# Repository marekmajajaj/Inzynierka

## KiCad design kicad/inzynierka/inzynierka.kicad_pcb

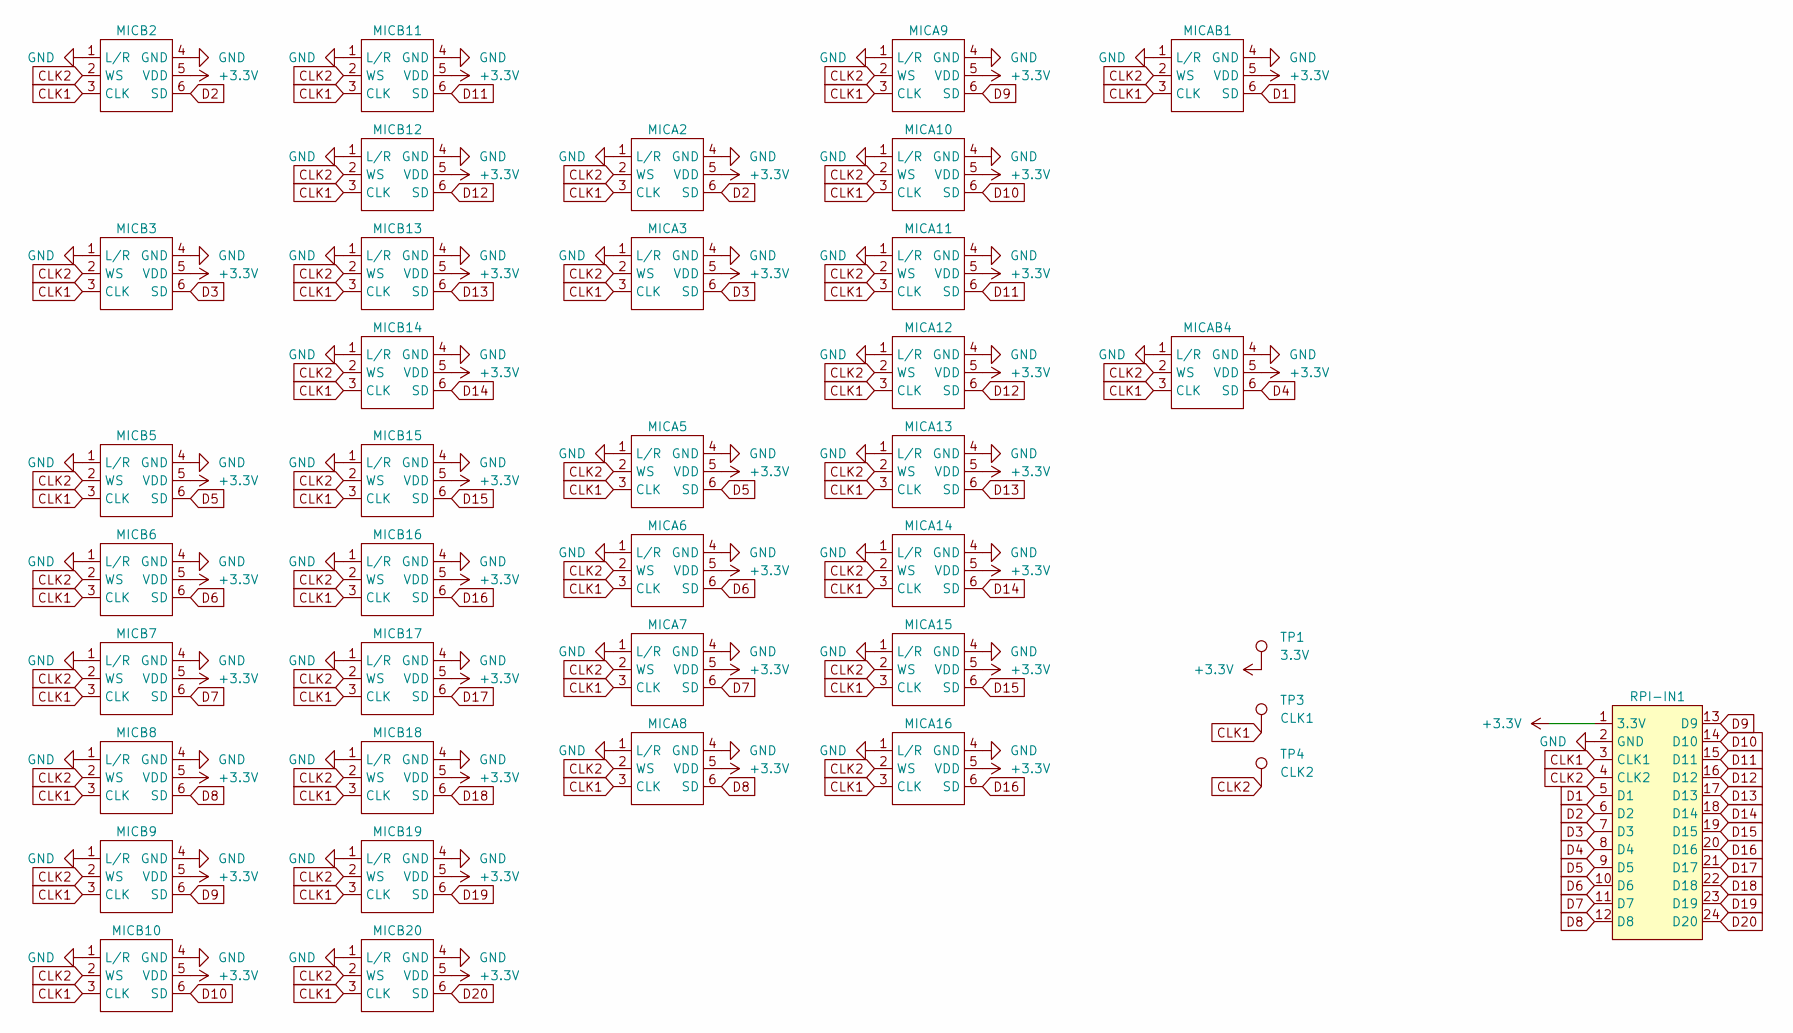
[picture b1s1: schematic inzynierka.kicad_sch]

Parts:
MICA2, MICA3, MICA5, MICA6, MICA7, MICA8, MICA9, MICA10, MICA11, MICA12, MICA13, MICA14, MICA15, MICA16: INMP441 breakout
MICAB1, MICAB4: INMP441 breakout
MICB2, MICB3, MICB5, MICB6, MICB7, MICB8, MICB9, MICB10, MICB11, MICB12, MICB13, MICB14, MICB15, MICB16, MICB17, MICB18, MICB19, MICB20: INMP441 breakout
RPI-IN1: RPI-IN1
TP1: 3.3V
TP3: CLK1
TP4: CLK2

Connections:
+3.3V: MICA2.5 (VDD), MICA3.5 (VDD), MICA5.5 (VDD), MICA6.5 (VDD), MICA7.5 (VDD), MICA8.5 (VDD), MICA9.5 (VDD), MICA10.5 (VDD), MICA11.5 (VDD), MICA12.5 (VDD), MICA13.5 (VDD), MICA14.5 (VDD), MICA15.5 (VDD), MICA16.5 (VDD), MICAB1.5 (VDD), MICAB4.5 (VDD), MICB2.5 (VDD), MICB3.5 (VDD), MICB5.5 (VDD), MICB6.5 (VDD), MICB7.5 (VDD), MICB8.5 (VDD), MICB9.5 (VDD), MICB10.5 (VDD), MICB11.5 (VDD), MICB12.5 (VDD), MICB13.5 (VDD), MICB14.5 (VDD), MICB15.5 (VDD), MICB16.5 (VDD), MICB17.5 (VDD), MICB18.5 (VDD), MICB19.5 (VDD), MICB20.5 (VDD), RPI-IN1.1 (3.3V), TP1.1; also elsewhere on the board
CLK1: MICA2.3 (CLK), MICA3.3 (CLK), MICA5.3 (CLK), MICA6.3 (CLK), MICA7.3 (CLK), MICA8.3 (CLK), MICA9.3 (CLK), MICA10.3 (CLK), MICA11.3 (CLK), MICA12.3 (CLK), MICA13.3 (CLK), MICA14.3 (CLK), MICA15.3 (CLK), MICA16.3 (CLK), MICAB1.3 (CLK), MICAB4.3 (CLK), MICB2.3 (CLK), MICB3.3 (CLK), MICB5.3 (CLK), MICB6.3 (CLK), MICB7.3 (CLK), MICB8.3 (CLK), MICB9.3 (CLK), MICB10.3 (CLK), MICB11.3 (CLK), MICB12.3 (CLK), MICB13.3 (CLK), MICB14.3 (CLK), MICB15.3 (CLK), MICB16.3 (CLK), MICB17.3 (CLK), MICB18.3 (CLK), MICB19.3 (CLK), MICB20.3 (CLK), RPI-IN1.3 (CLK1), TP3.1; also elsewhere on the board
CLK2: MICA2.2 (WS), MICA3.2 (WS), MICA5.2 (WS), MICA6.2 (WS), MICA7.2 (WS), MICA8.2 (WS), MICA9.2 (WS), MICA10.2 (WS), MICA11.2 (WS), MICA12.2 (WS), MICA13.2 (WS), MICA14.2 (WS), MICA15.2 (WS), MICA16.2 (WS), MICAB1.2 (WS), MICAB4.2 (WS), MICB2.2 (WS), MICB3.2 (WS), MICB5.2 (WS), MICB6.2 (WS), MICB7.2 (WS), MICB8.2 (WS), MICB9.2 (WS), MICB10.2 (WS), MICB11.2 (WS), MICB12.2 (WS), MICB13.2 (WS), MICB14.2 (WS), MICB15.2 (WS), MICB16.2 (WS), MICB17.2 (WS), MICB18.2 (WS), MICB19.2 (WS), MICB20.2 (WS), RPI-IN1.4 (CLK2), TP4.1; also elsewhere on the board
D1: MICAB1.6 (SD), RPI-IN1.5 (D1)
D2: MICA2.6 (SD), MICB2.6 (SD), RPI-IN1.6 (D2)
D3: MICA3.6 (SD), MICB3.6 (SD), RPI-IN1.7 (D3)
D4: MICAB4.6 (SD), RPI-IN1.8 (D4)
D5: MICA5.6 (SD), MICB5.6 (SD), RPI-IN1.9 (D5)
D6: MICA6.6 (SD), MICB6.6 (SD), RPI-IN1.10 (D6)
D7: MICA7.6 (SD), MICB7.6 (SD), RPI-IN1.11 (D7)
D8: MICA8.6 (SD), MICB8.6 (SD), RPI-IN1.12 (D8)
D9: MICA9.6 (SD), MICB9.6 (SD), RPI-IN1.13 (D9)
D10: MICA10.6 (SD), MICB10.6 (SD), RPI-IN1.14 (D10)
D11: MICA11.6 (SD), MICB11.6 (SD), RPI-IN1.15 (D11)
D12: MICA12.6 (SD), MICB12.6 (SD), RPI-IN1.16 (D12)
D13: MICA13.6 (SD), MICB13.6 (SD), RPI-IN1.17 (D13)
D14: MICA14.6 (SD), MICB14.6 (SD), RPI-IN1.18 (D14)
D15: MICA15.6 (SD), MICB15.6 (SD), RPI-IN1.19 (D15)
D16: MICA16.6 (SD), MICB16.6 (SD), RPI-IN1.20 (D16)
D17: MICB17.6 (SD), RPI-IN1.21 (D17)
D18: MICB18.6 (SD), RPI-IN1.22 (D18)
D19: MICB19.6 (SD), RPI-IN1.23 (D19)
D20: MICB20.6 (SD), RPI-IN1.24 (D20)
GND: MICA2.1 (L/R), MICA2.4 (GND), MICA3.1 (L/R), MICA3.4 (GND), MICA5.1 (L/R), MICA5.4 (GND), MICA6.1 (L/R), MICA6.4 (GND), MICA7.1 (L/R), MICA7.4 (GND), MICA8.1 (L/R), MICA8.4 (GND), MICA9.1 (L/R), MICA9.4 (GND), MICA10.1 (L/R), MICA10.4 (GND), MICA11.1 (L/R), MICA11.4 (GND), MICA12.1 (L/R), MICA12.4 (GND), MICA13.1 (L/R), MICA13.4 (GND), MICA14.1 (L/R), MICA14.4 (GND), MICA15.1 (L/R), MICA15.4 (GND), MICA16.1 (L/R), MICA16.4 (GND), MICAB1.1 (L/R), MICAB1.4 (GND), MICAB4.1 (L/R), MICAB4.4 (GND), MICB2.1 (L/R), MICB2.4 (GND), MICB3.1 (L/R), MICB3.4 (GND), MICB5.1 (L/R), MICB5.4 (GND), MICB6.1 (L/R), MICB6.4 (GND), MICB7.1 (L/R), MICB7.4 (GND), MICB8.1 (L/R), MICB8.4 (GND), MICB9.1 (L/R), MICB9.4 (GND), MICB10.1 (L/R), MICB10.4 (GND), MICB11.1 (L/R), MICB11.4 (GND), MICB12.1 (L/R), MICB12.4 (GND), MICB13.1 (L/R), MICB13.4 (GND), MICB14.1 (L/R), MICB14.4 (GND), MICB15.1 (L/R), MICB15.4 (GND), MICB16.1 (L/R), MICB16.4 (GND), MICB17.1 (L/R), MICB17.4 (GND), MICB18.1 (L/R), MICB18.4 (GND), MICB19.1 (L/R), MICB19.4 (GND), MICB20.1 (L/R), MICB20.4 (GND), RPI-IN1.2 (GND)

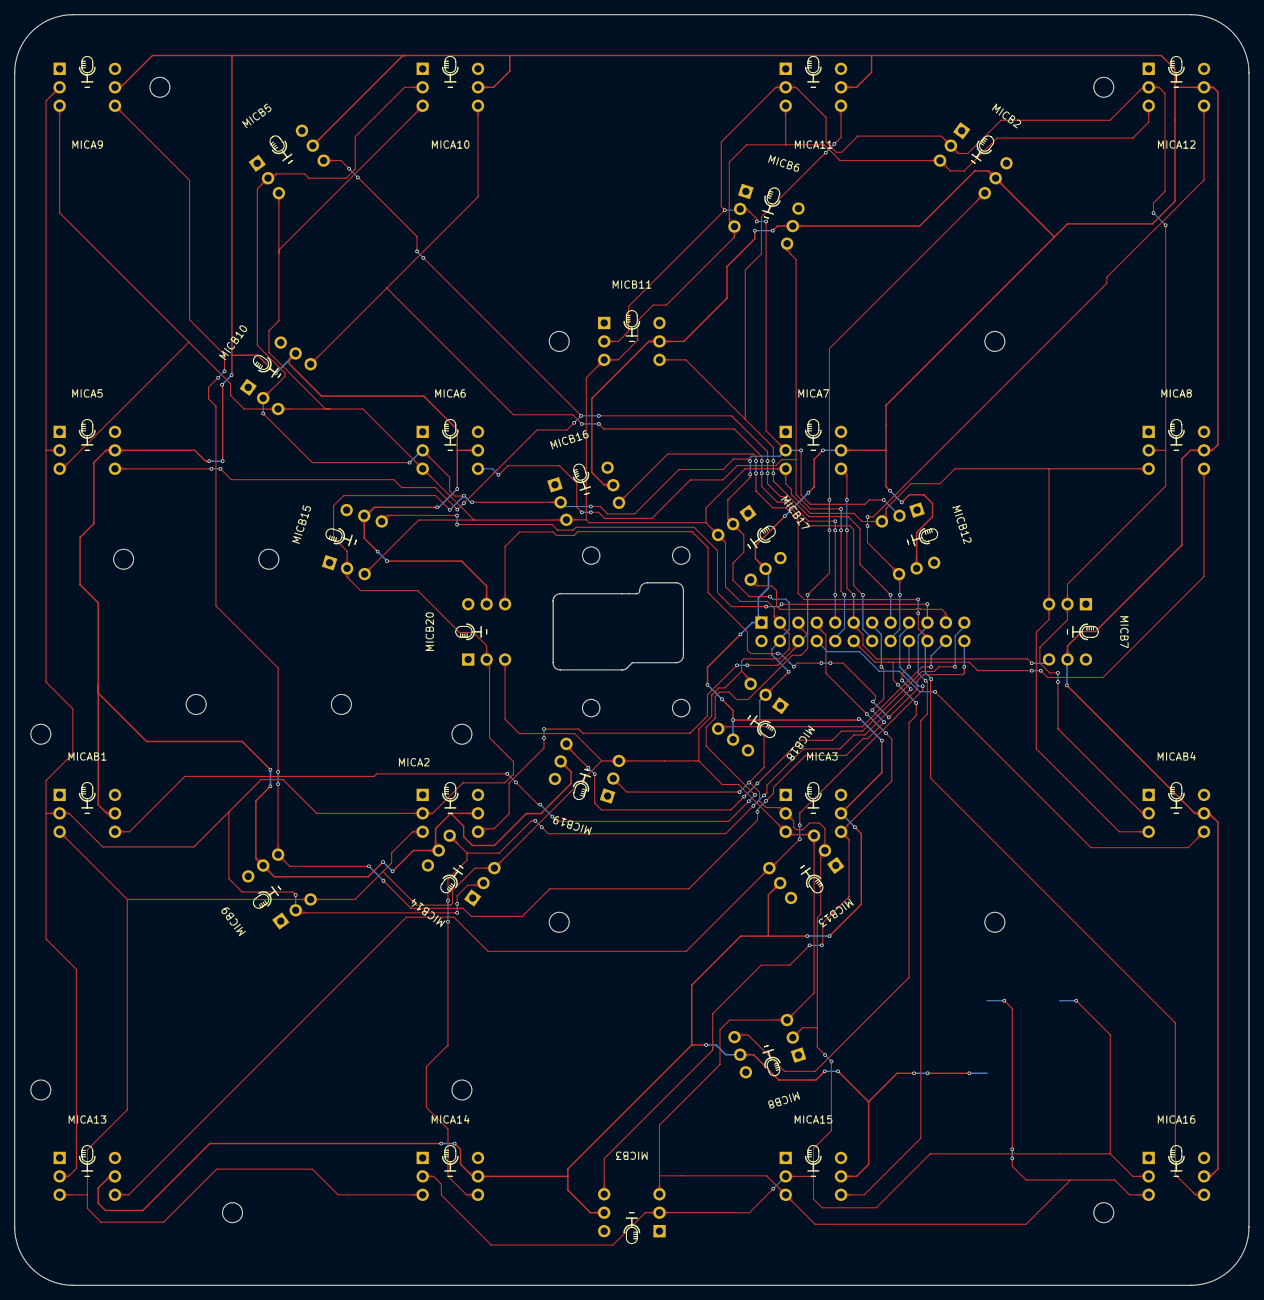
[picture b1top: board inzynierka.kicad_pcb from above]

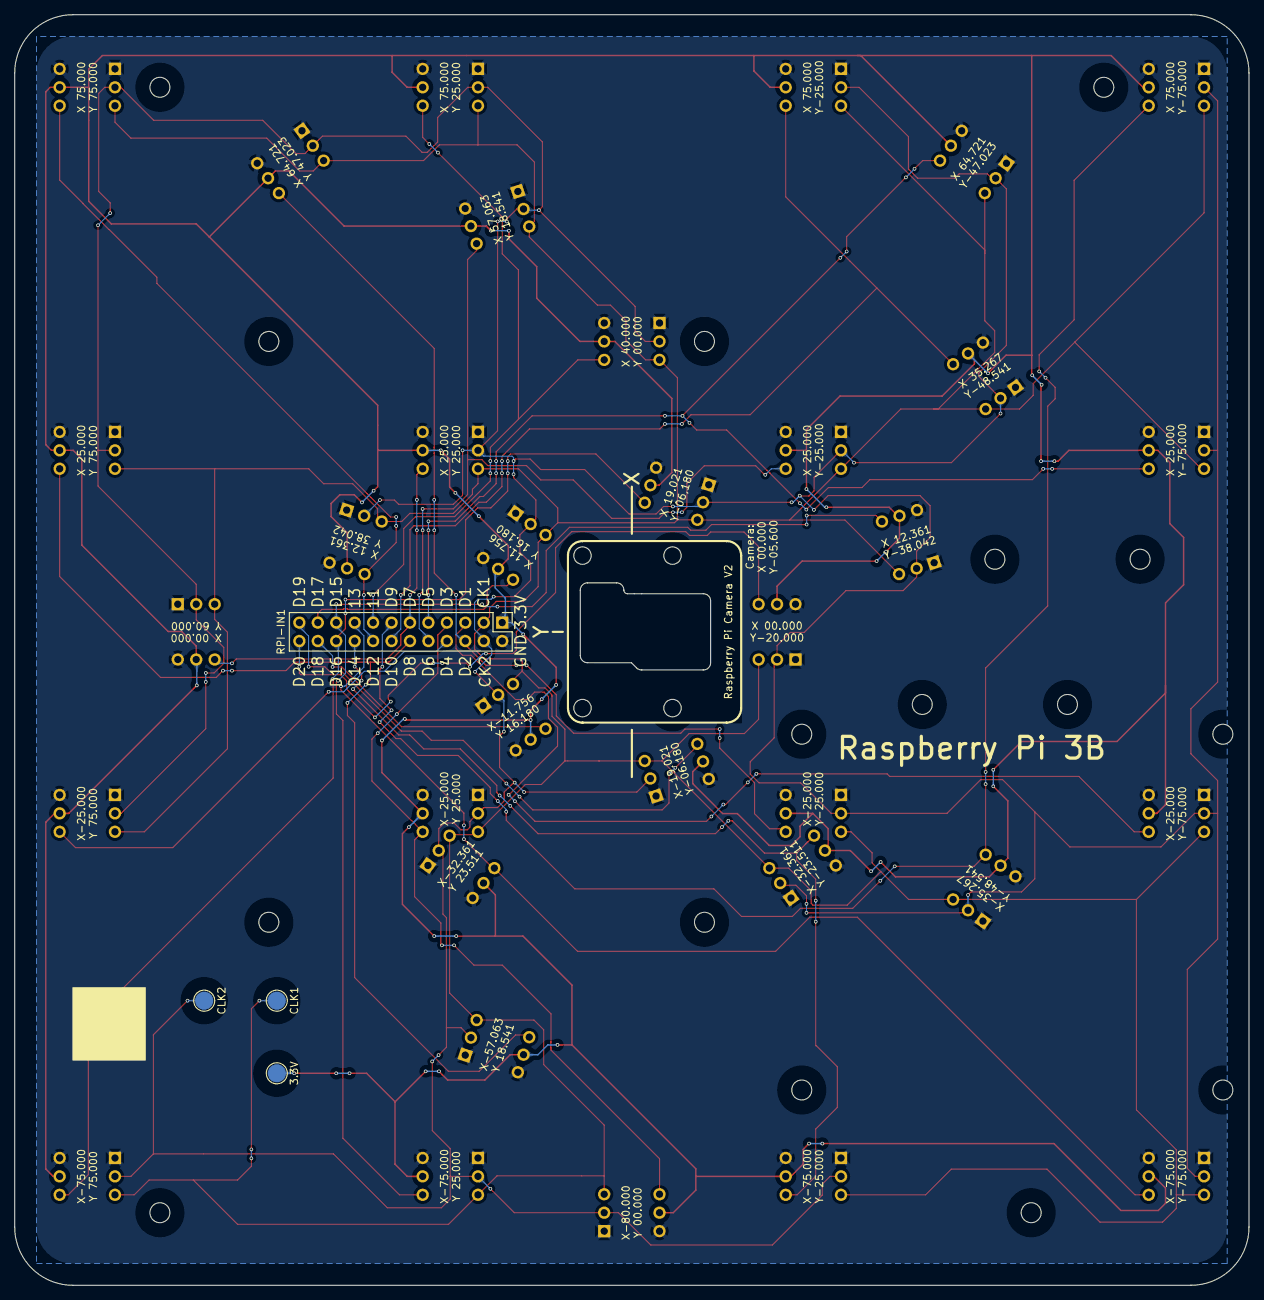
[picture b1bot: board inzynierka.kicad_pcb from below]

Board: 2 copper layers, 170.0 x 175.0 mm, 38 parts (4 on the bottom side), 24 nets.

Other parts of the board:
3.3V: 3.3V; TestPoint_Pad_D2.5mm
CLK1: CLK1; TestPoint_Pad_D2.5mm
CLK2: CLK2; TestPoint_Pad_D2.5mm

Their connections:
+3.3V: 3.3V.1; also elsewhere on the board
CLK1: CLK1.1; also elsewhere on the board
CLK2: CLK2.1; also elsewhere on the board

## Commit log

2025-12-13 Update gitignore
2025-12-13 Project start
2025-12-13 Przypisanie footprintów
2025-12-13 Added camera footprint
2025-12-14 Started routing
2025-12-14 Zmiana footprinta kamery
2025-12-14 Zaktualizowano gitignore
2025-12-15 Zaktualizowano do KiCad 9.0
2025-12-15 Dodanie pozycji mikrofonów B
2025-12-15 Dodanie biblioteki footprintów do projektu
2025-12-15 Dodanie innego ustawienia głośników na płytkę
2025-12-15 Dodanie opisów do footprintów
2025-12-15 Dodanie minimalnych właściwości fizycznych
2025-12-15 Dodanie listy przydatnych stron
2025-12-18 Coś tam porobione z płytką
2025-12-19 Dodanie trasowania dla CLK1 i linii danych + rozpoczęcie trasowania CLK2
2025-12-19 Dokończenie trasowania CLK2
2025-12-19 Podłączenie L/R na głośnikach do GND
2025-12-20 Dokończenie trasowania 3.3V
2025-12-20 Usunięcie błędów DRC dla 3.3V
2025-12-20 Uładnienie połączeń
2025-12-20 Pogrubienie footprintów + poprawienie trasowania
2025-12-20 Poprawa łączenia termicznego dla L/R w INMP441
2025-12-21 Zaokrąglenie płytki
2025-12-21 Dodanie dziur montażowych
2025-12-21 Poprawienie footprintu i odwrócenie kamery
2025-12-21 Przesunięto dziury montażowe dla RPI 3
2025-12-21 Rozpoczęcie dodawania opisów z tyłu płytki
2025-12-21 Dodanie podpisów lokalizacji mikrofonów
2025-12-21 Sprawdzenie ścieżek
2025-12-21 Dodanie oznaczenia na kod QR
2025-12-21 Zmiana pozycji kodu QR
2025-12-21 Zmniejszenie miedzi dla NTHP na kamerze
2025-12-21 Ostatecznie poprawki, chyba
2025-12-21 Poprawienie ograniczeń projektowych
2025-12-21 Zwiększenie rozmiaru przelotek
2025-12-21 Dodanie padów testowych
2025-12-21 Poszerzenie ścieżek do 0.14mm
2025-12-21 Poprawienie footprinta
2026-01-04 Dodanie kodu od fandahao17 i rozpoczecie dodawania obslugi GPIO
2026-01-04 Pobieranie GPIO za pomoca czytania rejestrow. Wlaczenie PMW.
2026-01-05 Dodanie pobierania danych na opadajacy sygnal PWM
2026-01-05 Powrocenie do sposobu z DMA
2026-01-06 Naprawiono bloki kontrolen DMA i ustawiono dobrze timingi
2026-01-06 Dodanie źródeł
2026-01-08 Dodanie wstępnej obróki danych
2026-01-13 Naprawienie niedziałającego pobierania dźwięku
2026-01-14 Dodanie plików z pozycjami mikrofonów
2026-01-15 Dodano kod generujący opóźnienia + zmieniono Makefile
2026-01-15 Poprawiono rzutowanie w calculateDelay()
2026-01-15 Poprawienie obliczania kątów theta + Usunięcie błędów w funkcji calculateDelay()
2026-01-24 Zmienienie pinów danych + zwiększenie prescalera zegara dla stabilniejszych wyników
2026-02-05 Dodanie funkcji do filtrowania sygnałów i obliczania RMS
2026-02-05 Wstępna filtracja działa
2026-02-05 Heatmapa działa dobrze
2026-02-06 v1.0
